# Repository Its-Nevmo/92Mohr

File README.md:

# 92Mohr

Probably my largest project to date, I present the 92Mohr. It's a TKL+, as I call it, because it follows the standard 87-key tenkeyless keyboard layout plus an additional five keys above the arrow keys (which I would think would have been done before, but I guess not). Utilizing the ALPS keyswitch standard, I used Matias Quiet Click switches with KbParadise Vintage PBT keycaps. 

While the original design had an integrated microcontroller, I learned the hard way that SMD soldering is not easy if you do not have the correct tools. As such, the most recent active revision, V3, relies on a socketed microcontroller. In this case, I'm using the Elite-C, but a Pro Micro would work as well. I'm currently in the process of developing a fourth version, featuring an integrated microcontroller, universal switch sockets for people who want MX switches instead of ALPS, and possibly a rotary switch and OLED display.

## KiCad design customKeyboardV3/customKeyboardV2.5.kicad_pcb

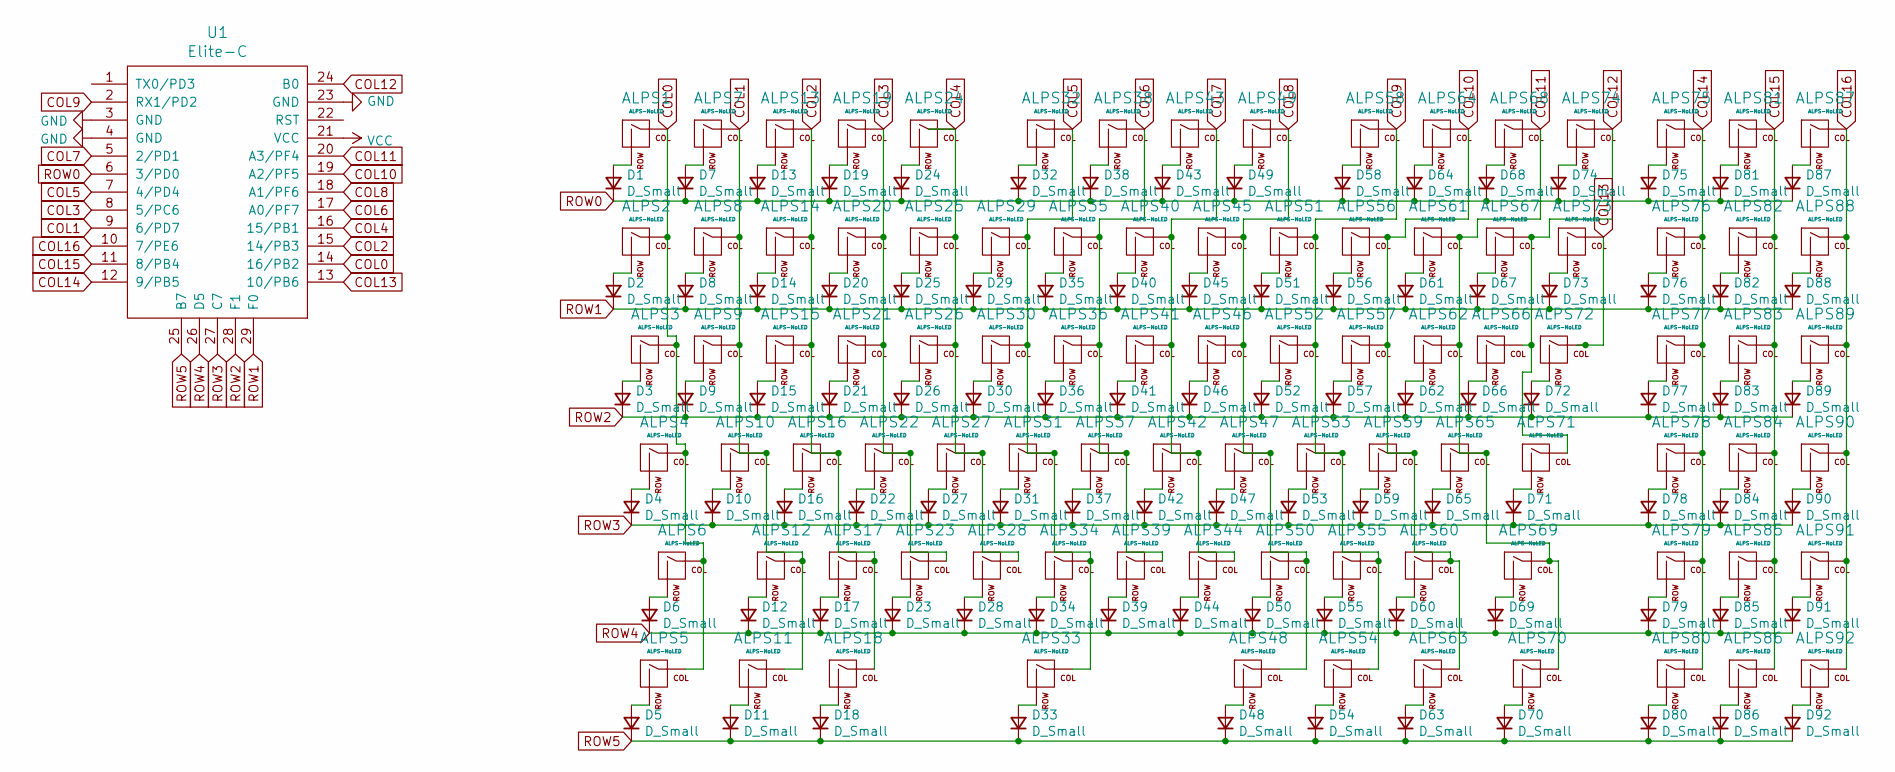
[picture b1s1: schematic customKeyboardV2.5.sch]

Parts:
ALPS1, ALPS2, ALPS7, ALPS8, ALPS9, ALPS10, ALPS12, ALPS13, ALPS14, ALPS15, ALPS16, ALPS17, ALPS19, ALPS20, ALPS21, ALPS22, ALPS23, ALPS24, ALPS25, ALPS26, ALPS27, ALPS28, ALPS29, ALPS30, ALPS31, ALPS32, ALPS34, ALPS35, ALPS36, ALPS37, ALPS38, ALPS39, ALPS40, ALPS41, ALPS42, ALPS43, ALPS44, ALPS45, ALPS46, ALPS47, ALPS49, ALPS50, ALPS51, ALPS52, ALPS53, ALPS55, ALPS56, ALPS57, ALPS58, ALPS59, ALPS60, ALPS61, ALPS62, ALPS64, ALPS65, ALPS66, ALPS67, ALPS68, ALPS74, ALPS75, ALPS76, ALPS77, ALPS78, ALPS79, ALPS80, ALPS81, ALPS82, ALPS83, ALPS84, ALPS85, ALPS86, ALPS87, ALPS88, ALPS89, ALPS90, ALPS91, ALPS92: ALPS-NoLED; ALPS-1U
ALPS3, ALPS72: ALPS-NoLED; ALPS-1.5U
ALPS4: ALPS-NoLED; ALPS-1.75U
ALPS5, ALPS11, ALPS18, ALPS48, ALPS54, ALPS63, ALPS70: ALPS-NoLED; ALPS-1.25U
ALPS6, ALPS71: ALPS-NoLED; ALPS-2.25U
ALPS33: ALPS-NoLED; ALPS-6.25U
ALPS69: ALPS-NoLED; ALPS-2.75U
ALPS73: ALPS-NoLED; ALPS-2U
D1, D2, D3, D4, D5, D6, D7, D8, D9, D10, D11, D12, D13, D14, D15, D16, D17, D18, D19, D20, D21, D22, D23, D24, D25, D26, D27, D28, D29, D30, D31, D32, D33, D34, D35, D36, D37, D38, D39, D40, D41, D42, D43, D44, D45, D46, D47, D48, D49, D50, D51, D52, D53, D54, D55, D56, D57, D58, D59, D60, D61, D62, D63, D64, D65, D66, D67, D68, D69, D70, D71, D72, D73, D74, D75, D76, D77, D78, D79, D80, D81, D82, D83, D84, D85, D86, D87, D88, D89, D90, D91, D92: D_Small; D_SOD-123
U1: Elite-C; Elite-C-castellated-29pin-holes-nopads

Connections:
COL0: ALPS1.1 (COL), ALPS2.1 (COL), ALPS3.1 (COL), ALPS4.1 (COL), ALPS5.1 (COL), ALPS6.1 (COL), U1.14 (16/PB2)
COL1: ALPS7.1 (COL), ALPS8.1 (COL), ALPS9.1 (COL), ALPS10.1 (COL), ALPS11.1 (COL), ALPS12.1 (COL), U1.9 (6/PD7)
COL2: ALPS13.1 (COL), ALPS14.1 (COL), ALPS15.1 (COL), ALPS16.1 (COL), ALPS17.1 (COL), ALPS18.1 (COL), U1.15 (14/PB3)
COL3: ALPS19.1 (COL), ALPS20.1 (COL), ALPS21.1 (COL), ALPS22.1 (COL), ALPS23.1 (COL), U1.8 (5/PC6)
COL4: ALPS24.1 (COL), ALPS25.1 (COL), ALPS26.1 (COL), ALPS27.1 (COL), ALPS28.1 (COL), U1.16 (15/PB1)
COL5: ALPS29.1 (COL), ALPS30.1 (COL), ALPS31.1 (COL), ALPS32.1 (COL), ALPS33.1 (COL), ALPS34.1 (COL), U1.7 (4/PD4)
COL6: ALPS35.1 (COL), ALPS36.1 (COL), ALPS37.1 (COL), ALPS38.1 (COL), ALPS39.1 (COL), U1.17 (A0/PF7)
COL7: ALPS40.1 (COL), ALPS41.1 (COL), ALPS42.1 (COL), ALPS43.1 (COL), ALPS44.1 (COL), U1.5 (2/PD1)
COL8: ALPS45.1 (COL), ALPS46.1 (COL), ALPS47.1 (COL), ALPS48.1 (COL), ALPS49.1 (COL), ALPS50.1 (COL), U1.18 (A1/PF6)
COL9: ALPS51.1 (COL), ALPS52.1 (COL), ALPS53.1 (COL), ALPS54.1 (COL), ALPS55.1 (COL), ALPS58.1 (COL), U1.2 (RX1/PD2)
COL10: ALPS56.1 (COL), ALPS57.1 (COL), ALPS59.1 (COL), ALPS60.1 (COL), ALPS63.1 (COL), ALPS64.1 (COL), U1.19 (A2/PF5)
COL11: ALPS61.1 (COL), ALPS62.1 (COL), ALPS65.1 (COL), ALPS68.1 (COL), ALPS69.1 (COL), ALPS70.1 (COL), U1.20 (A3/PF4)
COL12: ALPS66.1 (COL), ALPS67.1 (COL), ALPS71.1 (COL), ALPS74.1 (COL), U1.24 (B0)
COL13: ALPS72.1 (COL), ALPS73.1 (COL), U1.13 (10/PB6)
COL14: ALPS75.1 (COL), ALPS76.1 (COL), ALPS77.1 (COL), ALPS78.1 (COL), ALPS79.1 (COL), ALPS80.1 (COL), U1.12 (9/PB5)
COL15: ALPS81.1 (COL), ALPS82.1 (COL), ALPS83.1 (COL), ALPS84.1 (COL), ALPS85.1 (COL), ALPS86.1 (COL), U1.11 (8/PB4)
COL16: ALPS87.1 (COL), ALPS88.1 (COL), ALPS89.1 (COL), ALPS90.1 (COL), ALPS91.1 (COL), ALPS92.1 (COL), U1.10 (7/PE6)
GND: U1.3 (GND), U1.4 (GND), U1.23 (GND)
unnamed: ALPS1.2 (ROW), D1.2 (A)
unnamed: ALPS2.2 (ROW), D2.2 (A)
unnamed: ALPS3.2 (ROW), D3.2 (A)
unnamed: ALPS4.2 (ROW), D4.2 (A)
unnamed: ALPS5.2 (ROW), D5.2 (A)
unnamed: ALPS6.2 (ROW), D6.2 (A)
unnamed: ALPS7.2 (ROW), D7.2 (A)
unnamed: ALPS8.2 (ROW), D8.2 (A)
unnamed: ALPS9.2 (ROW), D9.2 (A)
unnamed: ALPS10.2 (ROW), D10.2 (A)
unnamed: ALPS11.2 (ROW), D11.2 (A)
unnamed: ALPS12.2 (ROW), D12.2 (A)
unnamed: ALPS13.2 (ROW), D13.2 (A)
unnamed: ALPS14.2 (ROW), D14.2 (A)
unnamed: ALPS15.2 (ROW), D15.2 (A)
unnamed: ALPS16.2 (ROW), D16.2 (A)
unnamed: ALPS17.2 (ROW), D17.2 (A)
unnamed: ALPS18.2 (ROW), D18.2 (A)
unnamed: ALPS19.2 (ROW), D19.2 (A)
unnamed: ALPS20.2 (ROW), D20.2 (A)
unnamed: ALPS21.2 (ROW), D21.2 (A)
unnamed: ALPS22.2 (ROW), D22.2 (A)
unnamed: ALPS23.2 (ROW), D23.2 (A)
unnamed: ALPS24.2 (ROW), D24.2 (A)
unnamed: ALPS25.2 (ROW), D25.2 (A)
unnamed: ALPS26.2 (ROW), D26.2 (A)
unnamed: ALPS27.2 (ROW), D27.2 (A)
unnamed: ALPS28.2 (ROW), D28.2 (A)
unnamed: ALPS29.2 (ROW), D29.2 (A)
unnamed: ALPS30.2 (ROW), D30.2 (A)
unnamed: ALPS31.2 (ROW), D31.2 (A)
unnamed: ALPS32.2 (ROW), D32.2 (A)
unnamed: ALPS33.2 (ROW), D33.2 (A)
unnamed: ALPS34.2 (ROW), D34.2 (A)
unnamed: ALPS35.2 (ROW), D35.2 (A)
unnamed: ALPS36.2 (ROW), D36.2 (A)
unnamed: ALPS37.2 (ROW), D37.2 (A)
unnamed: ALPS38.2 (ROW), D38.2 (A)
unnamed: ALPS39.2 (ROW), D39.2 (A)
unnamed: ALPS40.2 (ROW), D40.2 (A)
unnamed: ALPS41.2 (ROW), D41.2 (A)
unnamed: ALPS42.2 (ROW), D42.2 (A)
unnamed: ALPS43.2 (ROW), D43.2 (A)
unnamed: ALPS44.2 (ROW), D44.2 (A)
unnamed: ALPS45.2 (ROW), D45.2 (A)
unnamed: ALPS46.2 (ROW), D46.2 (A)
unnamed: ALPS47.2 (ROW), D47.2 (A)
unnamed: ALPS48.2 (ROW), D48.2 (A)
unnamed: ALPS49.2 (ROW), D49.2 (A)
unnamed: ALPS50.2 (ROW), D50.2 (A)
unnamed: ALPS51.2 (ROW), D51.2 (A)
unnamed: ALPS52.2 (ROW), D52.2 (A)
unnamed: ALPS53.2 (ROW), D53.2 (A)
unnamed: ALPS54.2 (ROW), D54.2 (A)
unnamed: ALPS55.2 (ROW), D55.2 (A)
unnamed: ALPS56.2 (ROW), D56.2 (A)
unnamed: ALPS57.2 (ROW), D57.2 (A)
unnamed: ALPS58.2 (ROW), D58.2 (A)
unnamed: ALPS59.2 (ROW), D59.2 (A)
unnamed: ALPS60.2 (ROW), D60.2 (A)
unnamed: ALPS61.2 (ROW), D61.2 (A)
unnamed: ALPS62.2 (ROW), D62.2 (A)
unnamed: ALPS63.2 (ROW), D63.2 (A)
unnamed: ALPS64.2 (ROW), D64.2 (A)
unnamed: ALPS65.2 (ROW), D65.2 (A)
unnamed: ALPS66.2 (ROW), D66.2 (A)
unnamed: ALPS67.2 (ROW), D67.2 (A)
unnamed: ALPS68.2 (ROW), D68.2 (A)
unnamed: ALPS69.2 (ROW), D69.2 (A)
unnamed: ALPS70.2 (ROW), D70.2 (A)
unnamed: ALPS71.2 (ROW), D71.2 (A)
unnamed: ALPS72.2 (ROW), D72.2 (A)
unnamed: ALPS73.2 (ROW), D73.2 (A)
unnamed: ALPS74.2 (ROW), D74.2 (A)
unnamed: ALPS75.2 (ROW), D75.2 (A)
unnamed: ALPS76.2 (ROW), D76.2 (A)
unnamed: ALPS77.2 (ROW), D77.2 (A)
unnamed: ALPS78.2 (ROW), D78.2 (A)
unnamed: ALPS79.2 (ROW), D79.2 (A)
unnamed: ALPS80.2 (ROW), D80.2 (A)
unnamed: ALPS81.2 (ROW), D81.2 (A)
unnamed: ALPS82.2 (ROW), D82.2 (A)
unnamed: ALPS83.2 (ROW), D83.2 (A)
unnamed: ALPS84.2 (ROW), D84.2 (A)
unnamed: ALPS85.2 (ROW), D85.2 (A)
unnamed: ALPS86.2 (ROW), D86.2 (A)
unnamed: ALPS87.2 (ROW), D87.2 (A)
unnamed: ALPS88.2 (ROW), D88.2 (A)
unnamed: ALPS89.2 (ROW), D89.2 (A)
unnamed: ALPS90.2 (ROW), D90.2 (A)
unnamed: ALPS91.2 (ROW), D91.2 (A)
unnamed: ALPS92.2 (ROW), D92.2 (A)
ROW0: D1.1 (K), D7.1 (K), D13.1 (K), D19.1 (K), D24.1 (K), D32.1 (K), D38.1 (K), D43.1 (K), D49.1 (K), D58.1 (K), D64.1 (K), D68.1 (K), D74.1 (K), D75.1 (K), D81.1 (K), D87.1 (K), U1.6 (3/PD0)
ROW1: D2.1 (K), D8.1 (K), D14.1 (K), D20.1 (K), D25.1 (K), D29.1 (K), D35.1 (K), D40.1 (K), D45.1 (K), D51.1 (K), D56.1 (K), D61.1 (K), D67.1 (K), D73.1 (K), D76.1 (K), D82.1 (K), D88.1 (K), U1.29 (F0)
ROW2: D3.1 (K), D9.1 (K), D15.1 (K), D21.1 (K), D26.1 (K), D30.1 (K), D36.1 (K), D41.1 (K), D46.1 (K), D52.1 (K), D57.1 (K), D62.1 (K), D66.1 (K), D72.1 (K), D77.1 (K), D83.1 (K), D89.1 (K), U1.28 (F1)
ROW3: D4.1 (K), D10.1 (K), D16.1 (K), D22.1 (K), D27.1 (K), D31.1 (K), D37.1 (K), D42.1 (K), D47.1 (K), D53.1 (K), D59.1 (K), D65.1 (K), D71.1 (K), D78.1 (K), D84.1 (K), D90.1 (K), U1.27 (C7)
ROW4: D6.1 (K), D12.1 (K), D17.1 (K), D23.1 (K), D28.1 (K), D34.1 (K), D39.1 (K), D44.1 (K), D50.1 (K), D55.1 (K), D60.1 (K), D69.1 (K), D79.1 (K), D85.1 (K), D91.1 (K), U1.26 (D5)
ROW5: D5.1 (K), D11.1 (K), D18.1 (K), D33.1 (K), D48.1 (K), D54.1 (K), D63.1 (K), D70.1 (K), D80.1 (K), D86.1 (K), D92.1 (K), U1.25 (B7)
VCC: U1.21 (VCC)

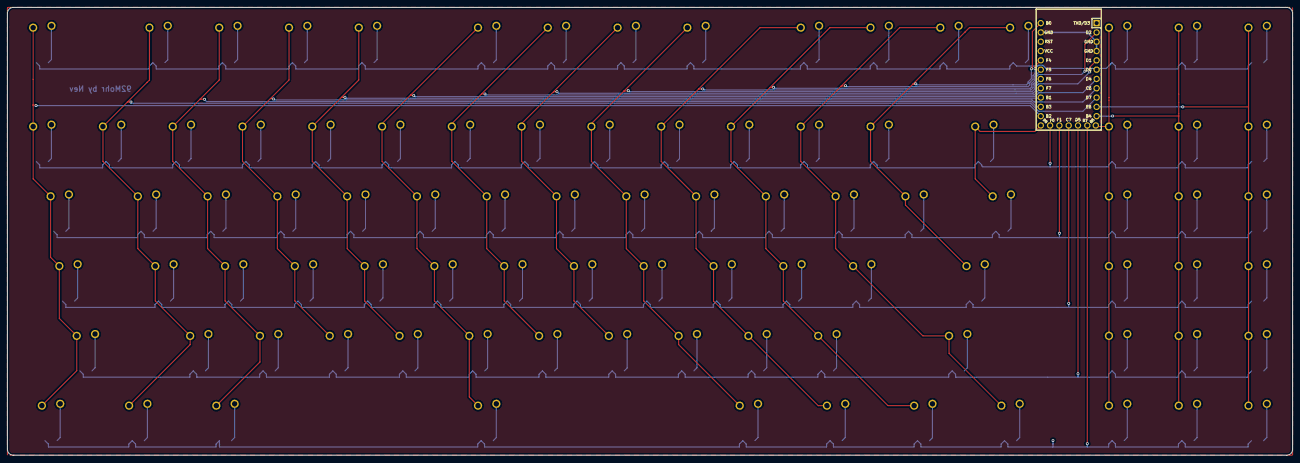
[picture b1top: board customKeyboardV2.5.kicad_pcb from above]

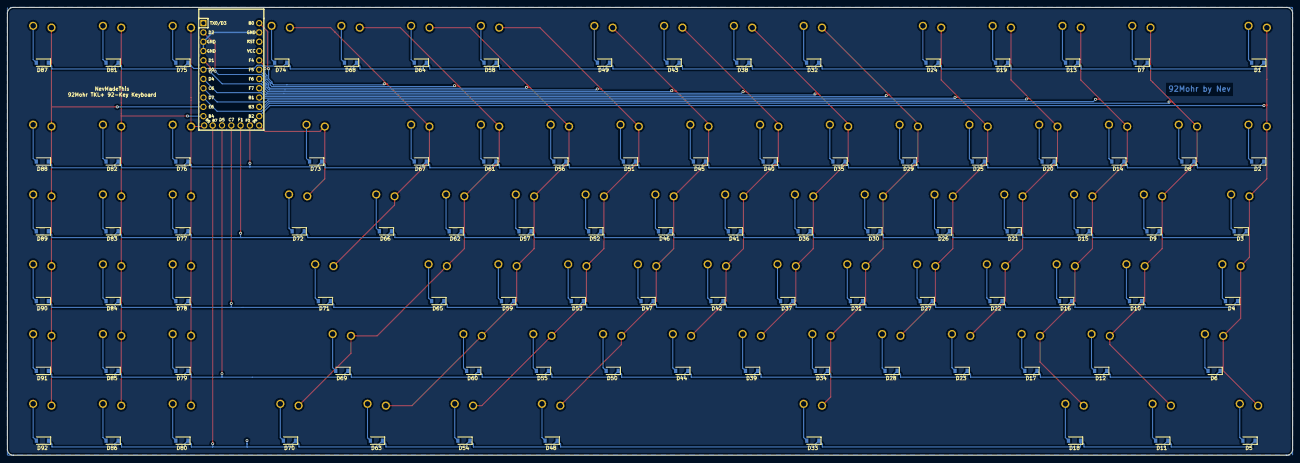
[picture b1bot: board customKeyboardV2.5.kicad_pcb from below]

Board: 2 copper layers, 350.8 x 122.2 mm, 185 parts (93 on the bottom side), 116 nets.

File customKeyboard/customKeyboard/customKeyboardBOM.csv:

"Id";"Designator";"Package";"Quantity";"Designation";"Supplier and ref";
1;"ALPS74,ALPS1,ALPS92,ALPS91,ALPS90,ALPS89,ALPS88,ALPS87,ALPS86,ALPS85,ALPS84,ALPS83,ALPS82,ALPS81,ALPS80,ALPS79,ALPS78,ALPS77,ALPS76,ALPS75,ALPS72,ALPS67,ALPS66,ALPS65,ALPS64,ALPS62,ALPS61,ALPS60,ALPS59,ALPS58,ALPS57,ALPS56,ALPS55,ALPS53,ALPS52,ALPS51,ALPS50,ALPS49,ALPS47,ALPS46,ALPS45,ALPS44,ALPS43,ALPS42,ALPS41,ALPS40,ALPS39,ALPS38,ALPS37,ALPS36,ALPS35,ALPS34,ALPS32,ALPS31,ALPS30,ALPS29,ALPS28,ALPS27,ALPS26,ALPS25,ALPS24,ALPS23,ALPS22,ALPS21,ALPS20,ALPS19,ALPS17,ALPS16,ALPS15,ALPS14,ALPS13,ALPS12,ALPS10,ALPS9,ALPS8,ALPS7,ALPS2";"ALPS-1U";77;"ALPS-NoLED";;;
2;"F1";"Fuse_1206_3216Metric";1;"500mA";;;
3;"R5,R6";"R_0805_2012Metric";2;"5k1";;;
4;"R2,R3";"R_0805_2012Metric";2;"22";;;
5;"C7,C6";"C_0805_2012Metric";2;"22pF";;;
6;"ALPS70,ALPS6";"ALPS-2.25U";2;"ALPS-NoLED";;;
7;"Y1";"Crystal_SMD_3225-4Pin_3.2x2.5mm";1;"16MHz";;;
8;"U1";"TQFP-44_10x10mm_P0.8mm";1;"ATmega32U4-AU";;;
9;"SW1";"SKQG-1155865";1;"SW_Push";;;
10;"R4,R1";"R_0805_2012Metric";2;"10k";;;
11;"J1";"USB_C_GCT_USB4085";1;"USB_C_Receptacle_USB2.0";;;
12;"D92,D91,D90,D89,D88,D87,D86,D85,D84,D83,D82,D81,D80,D79,D78,D77,D76,D75,D74,D73,D72,D71,D70,D69,D68,D67,D66,D65,D64,D63,D62,D61,D60,D59,D58,D57,D56,D55,D54,D53,D52,D51,D50,D49,D48,D47,D46,D45,D44,D43,D42,D41,D40,D39,D38,D37,D36,D35,D34,D33,D32,D31,D30,D29,D28,D27,D26,D25,D24,D23,D22,D21,D20,D19,D18,D17,D16,D15,D14,D13,D12,D11,D10,D9,D8,D7,D6,D5,D4,D3,D2,D1";"D_SOD-123";92;"D_Small";;;
13;"C5";"C_0805_2012Metric";1;"10uF";;;
14;"C4,C3,C2";"C_0805_2012Metric";3;"0.1uF";;;
15;"C1";"C_0805_2012Metric";1;"1uF";;;
16;"ALPS73";"ALPS-2U";1;"ALPS-NoLED";;;
17;"ALPS71,ALPS3";"ALPS-1.5U";2;"ALPS-NoLED";;;
18;"ALPS69,ALPS63,ALPS54,ALPS48,ALPS18,ALPS11,ALPS5";"ALPS-1.25U";7;"ALPS-NoLED";;;
19;"ALPS68";"ALPS-2.75U";1;"ALPS-NoLED";;;
20;"ALPS33";"ALPS-6.25U";1;"ALPS-NoLED";;;
21;"ALPS4";"ALPS-1.75U";1;"ALPS-NoLED";;;

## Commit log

2022-04-30 Add files via upload
    Init upload for all currently existing versions. Includes original version, newer versions, and photos of V3.
